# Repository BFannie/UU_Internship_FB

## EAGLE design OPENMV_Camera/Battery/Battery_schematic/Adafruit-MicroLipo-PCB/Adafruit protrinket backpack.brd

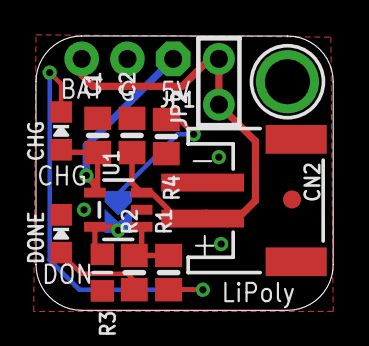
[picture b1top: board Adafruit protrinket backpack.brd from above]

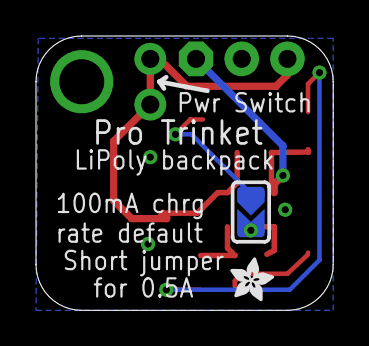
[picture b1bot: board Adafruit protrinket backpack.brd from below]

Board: 2 copper layers, 16.5 x 15.2 mm, 16 parts (2 on the bottom side), 8 nets.

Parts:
C1, C2: 10µF; 0805-NO
CHG: RED; CHIPLED_0805_NOOUTLINE
CN2: JSTPH; JSTPH2
DONE: GREEN; CHIPLED_0805_NOOUTLINE
FID1: FIDUCIAL""; FIDUCIAL_1MM
JP1: 1X03_ROUND_76
JP2: 1X02_ROUND
R1, R2: 1K; 0805-NO
R3: 10K\; _0805MP
R4: 2.5K; 0805-NO
SJ1: SOLDERJUMPER_ARROW_NOPASTE
U1: MCP73831T-2ACI/OT; SOT23-5
U$9: ADAFRUIT_2.5MM
U$10: MOUNTINGHOLE2.5; MOUNTINGHOLE_2.5_PLATED

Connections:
GND: C1.2, C2.2, CN2.1, DONE.C, JP1.2, R3.2, R4.2, U1.2
unnamed: CHG.C, R1.1
unnamed: R1.2, R2.2, U1.1
unnamed: R4.1, SJ1.1
unnamed: R3.1, SJ1.2, U1.5
unnamed: DONE.A, R2.1
VBAT: C2.1, CN2.2, JP1.3, JP2.1, JP2.2, U1.3
VBUS: C1.1, CHG.A, JP1.1, U1.4

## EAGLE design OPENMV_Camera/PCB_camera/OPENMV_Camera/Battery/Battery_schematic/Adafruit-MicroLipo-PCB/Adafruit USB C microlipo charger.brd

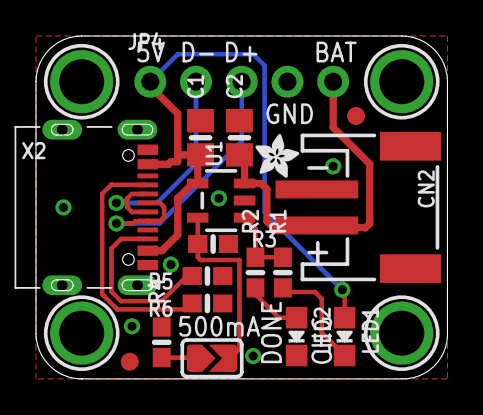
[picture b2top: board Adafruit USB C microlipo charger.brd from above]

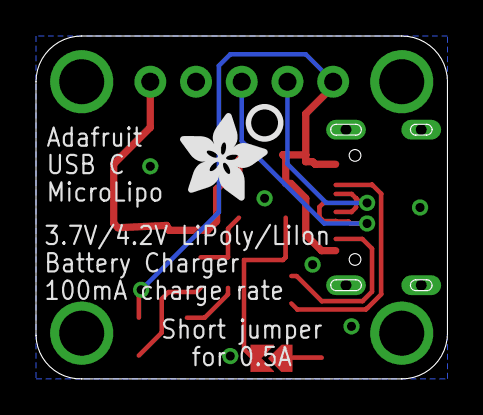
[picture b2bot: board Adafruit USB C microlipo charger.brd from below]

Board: 2 copper layers, 22.9 x 19.1 mm, 24 parts (2 on the bottom side), 12 nets.

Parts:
C1, C2: 10µF; 0805-NO@1
CN2: JSTPH; JSTPH2
FID1, FID2: FIDUCIAL""; FIDUCIAL_1MM
JP4: 1X05_ROUND_70
LED1: RED; CHIPLED_0805_NOOUTLINE
LED2: GREEN; CHIPLED_0805_NOOUTLINE
R1, R2: 470; 0603-NO
R3: 10K\; 0603-NO
R4: 2.2K; 0603-NO
R5, R6: 5.1K; 0603-NO
SJ1: SOLDERJUMPER_ARROW_NOPASTE
U1: MCP73831T-2ACI/OT; SOT23-5
U$2: ADAFRUIT_2.5MM
U$9, U$10, U$11, U$12: MOUNTINGHOLE2.5; MOUNTINGHOLE_2.5_PLATED
U$13: ADAFRUIT_5MM
U$16: PCBFEAT-REV-040
X2: USB_C_CUSB31-CFM2AX-01-X

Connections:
5V: C1.1, JP4.1, LED1.A, U1.4, X2.A4B9, X2.B4A9
CC1: R6.2, X2.A5
CC2: R5.2, X2.B5
D+: JP4.3, X2.A6, X2.B6
D-: JP4.2, X2.A7, X2.B7
GND: C1.2, C2.2, CN2.1, JP4.4, LED2.C, R3.2, R4.2, R5.1, R6.1, U1.2, X2.A1B12, X2.B1A12
unnamed: LED1.C, R1.1
unnamed: R1.2, R2.2, U1.1
unnamed: R4.1, SJ1.1
unnamed: R3.1, SJ1.2, U1.5
unnamed: LED2.A, R2.1
VBAT: C2.1, CN2.2, JP4.5, U1.3

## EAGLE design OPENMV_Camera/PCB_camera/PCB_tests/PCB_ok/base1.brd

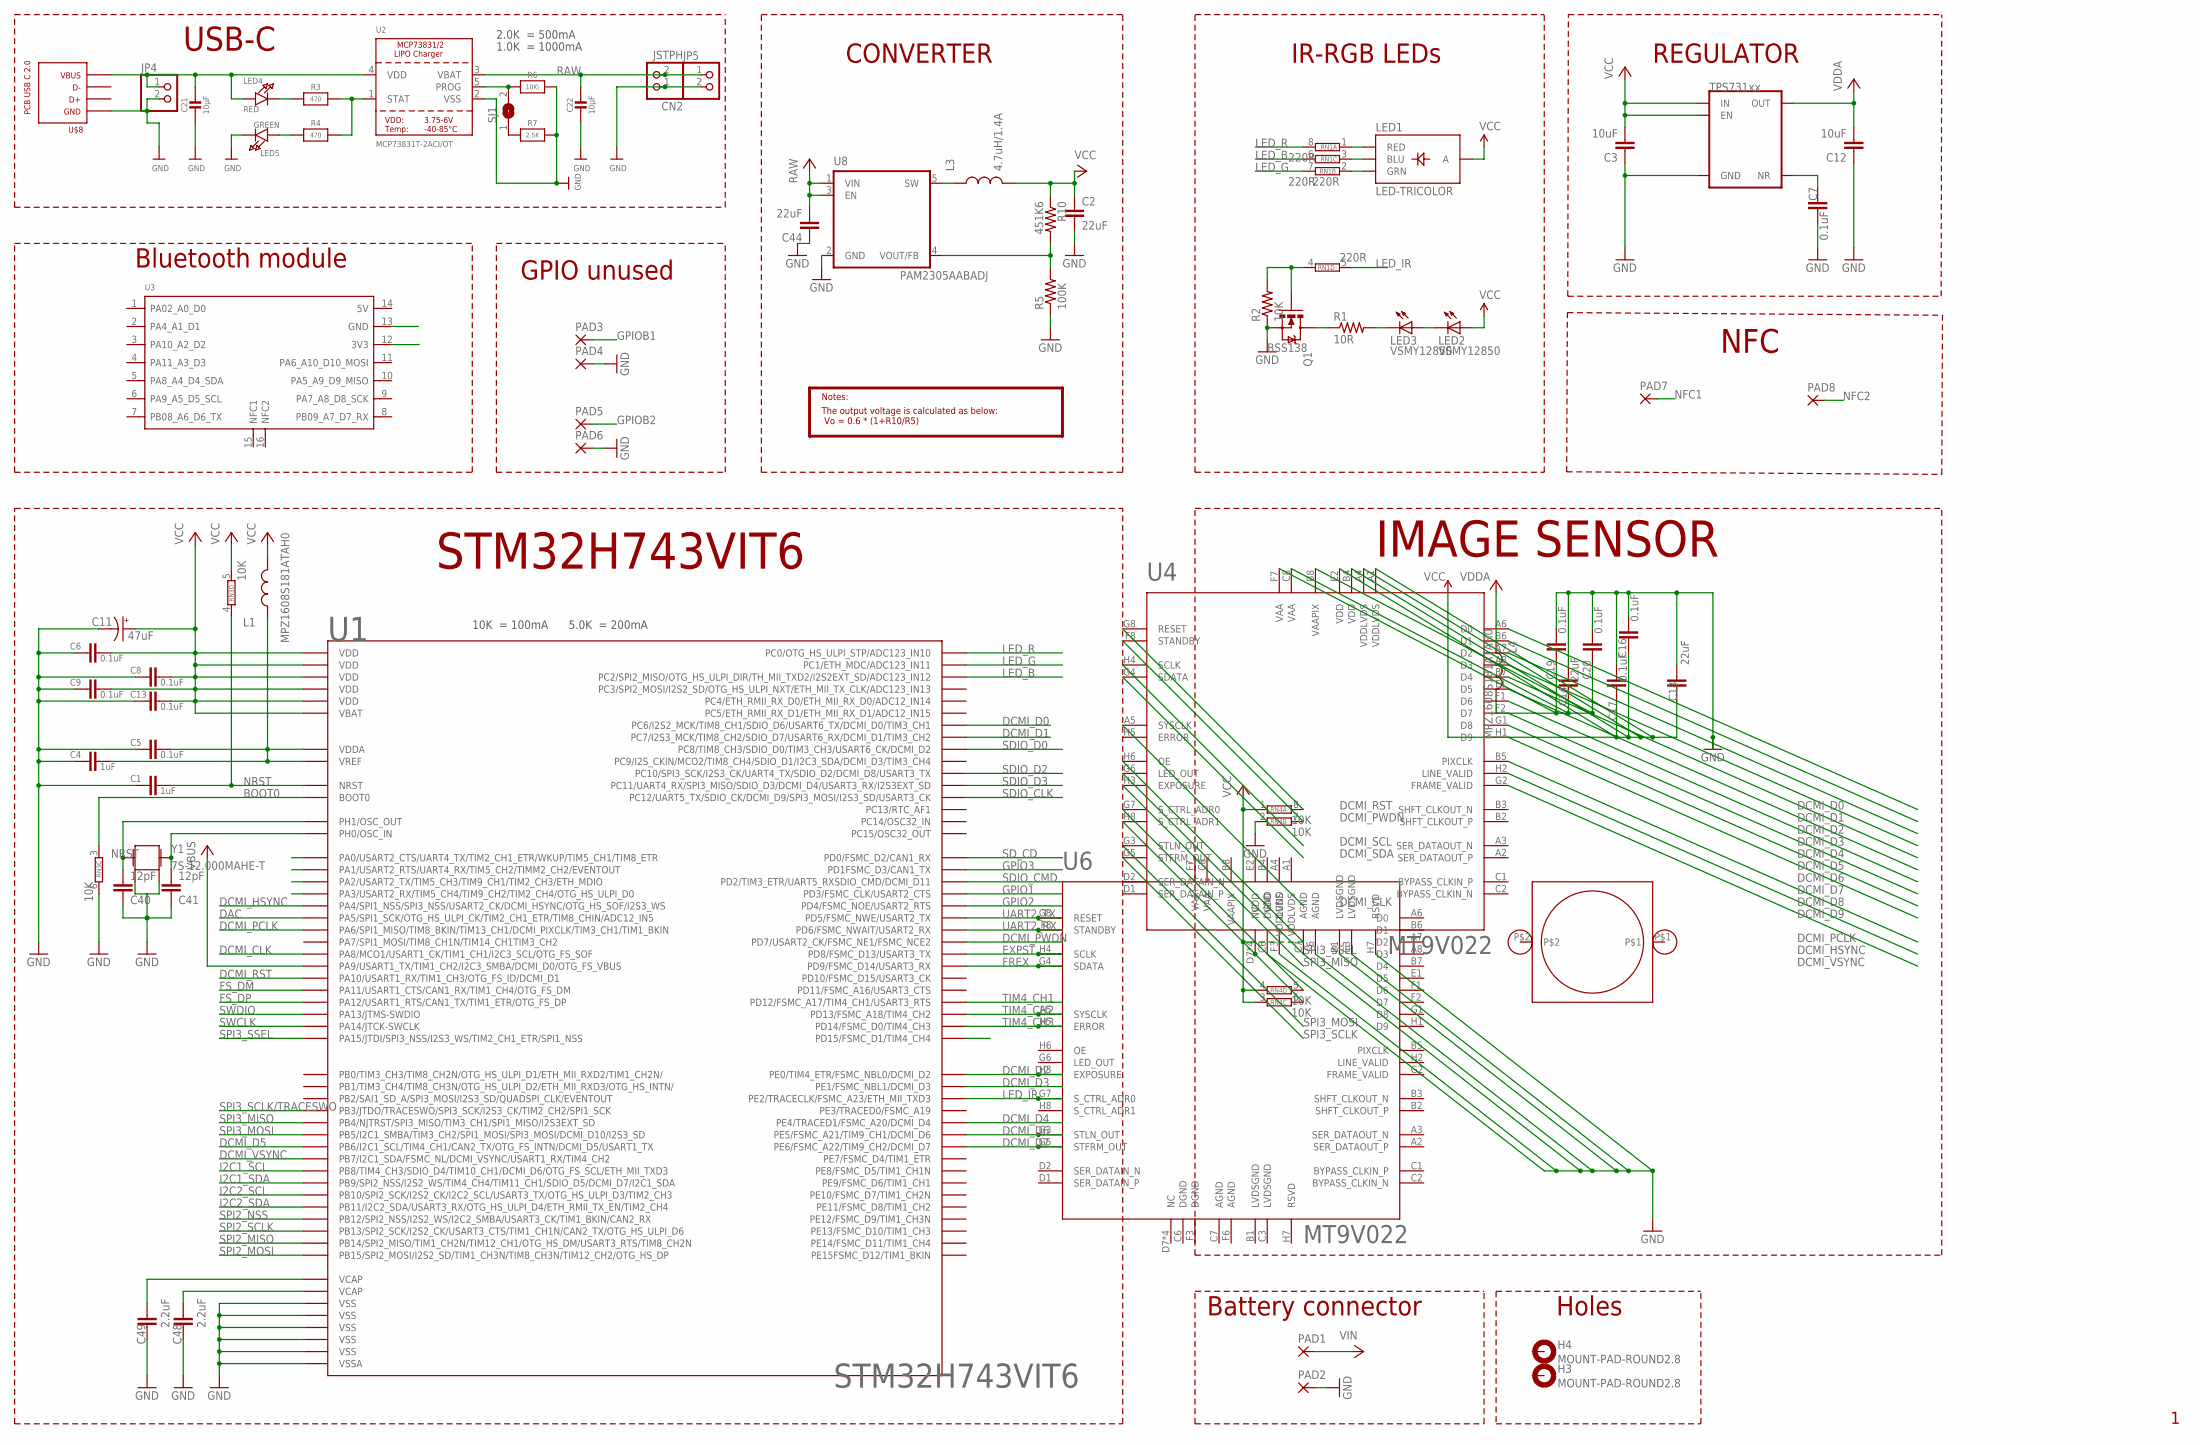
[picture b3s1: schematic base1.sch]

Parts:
C1, C4: 1uF; 0603-CAP
C2, C14, C18, C44: 22uF; 0805
C3, C12: 10uF; 0805
C5, C6, C7, C8, C9, C13: 0.1uF; 0603-CAP
C11: 47uF; EIA3216
C16, C17, C19, C20: 0.1uF; 0402-CAP
C21, C22: 10µF; 0805-NO
C40, C41: 12pF; 0603-CAP
C48, C49: 2.2uF; 0603-CAP
CN2: JSTPH; JSTPH2
H3, H4: MOUNT-PAD-ROUND2.8; 2,8-PAD
JP4, JP5: HEADER-1X2ROUND; 1X02_ROUND
L1, L4: MPZ1608S181ATAH0; 0603
L3: 4.7uH/1.4A; 1007
LED1: LED-TRICOLOR; LED-TRICOLOR-SMD-MF
LED2, LED3: VSMY12850; LED-1206
LED4: RED; CHIPLED_0805_NOOUTLINE
LED5: GREEN; CHIPLED_0805_NOOUTLINE
LM1: LENSMOUNT20MM; LENSMOUNT-20MM
PAD1, PAD2, PAD3, PAD4, PAD5, PAD6, PAD7, PAD8: SMD2; SMD1,27-2,54
Q1: BSS138; SOT23-3
R1: 10R; 0603-RES
R2: 10K; 0603-RES
R3, R4: 470; 0805-NO
R5: 100K; 0603-RES
R6: 10K\; 0805-NO
R7: 2.5K; 0805-NO
R10: 451K6; 0603-RES
RN1: 220R; EXBV8V
RN3, RN4: 10K; EXBV8V
SJ1: SOLDERJUMPER; SOLDERJUMPER_ARROW_NOPASTE
U1: STM32H743VIT6; LQFP100
U2: MCP73831T-2ACI/OT; SOT23-5
U3: MOUDLE-SEEEDUINO-XIAO-NRF52840-SENSE-SMD; MOUDLE16P-SMD-2.54-21X17.8MM
U4, U6: MT9V022; IBGA52
U5: TPS731XX; SOT23-5
U8: PAM2305AABADJ; TSOT25
U$8: PCB_USB_C_2.0DS_2; USB_TYPE_C_DS_2
Y1: 7S-12.000MAHE-T; CRYSTAL-2.5X2.0

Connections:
BOOT0: RN3.3 (1), U1.94 (BOOT0)
DAC: U1.29 (PA5/SPI1_SCK/OTG_HS_ULPI_CK/TIM2_CH1_ET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)
DCMI_CLK: U1.67 (PA8/MCO1/USART1_CK/TIM1_CH1/I2C3_SCL/OT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), U4.A5 (SYSCLK)
DCMI_D0: U1.63 (PC6/I2S2_MCK/TIM8_CH1/SDIO_D6/USART6_TX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), U4.A6 (D0)
DCMI_D1: U1.64 (PC7/I2S3_MCK/TIM8_CH2/SDIO_D7/USART6_RX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), U4.B6 (D1)
DCMI_D2: U1.97 (PE0/TIM4_ETR/FSMC_NBL0/DCMI_D2), U4.A7 (D2), U6.H3 (EXPOSURE)
DCMI_D3: U1.98 (PE1/FSMC_NBL1/DCMI_D3), U4.A8 (D3)
DCMI_D4: U1.3 (PE4/TRACED1/FSMC_A20/DCMI_D4), U4.B7 (D4)
DCMI_D5: U1.92 (PB6/I2C1_SCL/TIM4_CH1/CAN2_TX/OTG_FS_IN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), U4.E1 (D5)
DCMI_D6: U1.4 (PE5/FSMC_A21/TIM9_CH1/DCMI_D6), U4.F1 (D6), U6.G3 (STLN_OUT)
DCMI_D7: U1.5 (PE6/FSMC_A22/TIM9_CH2/DCMI_D7), U4.F2 (D7), U6.G5 (STFRM_OUT)
DCMI_D8: U4.G1 (D8)
DCMI_D9: U4.H1 (D9)
DCMI_HSYNC: U1.28 (PA4/SPI1_NSS/SPI3_NSS/USART2_CK/DCMI_HS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), U4.H2 (LINE_VALID)
DCMI_PCLK: U1.30 (PA6/SPI1_MISO/TIM8_BKIN/TIM13_CH1/DCMI_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), U4.B5 (PIXCLK)
DCMI_PWDN: RN4.7 (2), U1.88 (PD7/USART2_CK/FSMC_NE1/FSMC_NCE2), U4.F8 (STANDBY)
DCMI_RST: RN4.8 (2), U1.69 (PA10/USART1_RX/TIM1_CH3/OTG_FS_ID/DCMI_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), U4.G8 (RESET)
DCMI_SCL: U4.H4 (SCLK)
DCMI_SDA: U4.G4 (SDATA)
DCMI_VSYNC: U1.93 (PB7/I2C1_SDA/FSMC_NL/DCMI_VSYNC/USART1_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), U4.G2 (FRAME_VALID)
EXPST: U1.55 (PD8/FSMC_D13/USART3_TX), U6.H4 (SCLK)
FREX: U1.56 (PD9/FSMC_D14/USART3_RX), U6.G4 (SDATA)
FS_DM: U1.70 (PA11/USART1_CTS/CAN1_RX/TIM1_CH4/OTG_FS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)
FS_DP: U1.71 (PA12/USART1_RTS/CAN1_TX/TIM1_ETR/OTG_FS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)
GND: C1.2, C2.2, C3.1, C4.2, C5.2, C6.2, C7.2, C8.2, C9.2, C11.C (-), C12.1, C13.2, C14.1, C16.2, C17.2, C18.1, C19.2, C20.2, C21.2, C22.2, C40.1, C41.1, C44.1, C48.2, C49.2, CN2.1, JP4.2, JP5.2, LED5.C, PAD2.1, PAD4.1, PAD6.1, Q1.2 (S), R2.1, R5.1, R6.2, R7.2, RN3.6 (2), RN4.2 (1), U1.10 (VSS), U1.19 (VSSA), U1.26 (VSS), U1.49 (VSS), U1.74 (VSS), U1.99 (VSS), U2.2 (VSS), U4.B1 (LVDSGND), U4.C3 (LVDSGND), U4.C6 (DGND), U4.C7 (AGND), U4.F3 (DGND), U4.F6 (AGND), U4.H7 (RSVD), U5.2 (GND), U8.2 (GND), U$8.A4 (VBUS), U$8.A9 (VBUS), U$8.B4 (VBUS), U$8.B9 (VBUS), Y1.2, Y1.4
GPIO1: U1.84 (PD3/FSMC_CLK/USART2_CTS)
GPIO2: U1.85 (PD4/FSMC_NOE/USART2_RTS)
GPIO3: U1.82 (PD1FSMC_D3/CAN1_TX)
GPIOB1: PAD3.1
GPIOB2: PAD5.1
I2C1_SCL: U1.95 (PB8/TIM4_CH3/SDIO_D4/TIM10_CH1/DCMI_D6/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)
I2C1_SDA: U1.96 (PB9/SPI2_NSS/I2S2_WS/TIM4_CH4/TIM11_CH1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)
I2C2_SCL: U1.46 (PB10/SPI2_SCK/I2S2_CK/I2C2_SCL/USART3_T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)
I2C2_SDA: U1.47 (PB11/I2C2_SDA/USART3_RX/OTG_HS_ULPI_D4/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)
LED_B: RN1.6 (2), U1.17 (PC2/SPI2_MISO/OTG_HS_ULPI_DIR/TH_MII_TX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)
LED_G: RN1.7 (2), U1.16 (PC1/ETH_MDC/ADC123_IN11)
LED_IR: RN1.5 (2), U1.1 (PE2/TRACECLK/FSMC_A23/ETH_MII_TXD3), U6.G7 (S_CTRL_ADR0)
LED_R: RN1.8 (2), U1.15 (PC0/OTG_HS_ULPI_STP/ADC123_IN10)
unnamed: LED4.C, R3.1
unnamed: C40.2, U1.13 (PH1/OSC_OUT), Y1.3 (2)
unnamed: R3.2, R4.2, U2.1 (STAT)
unnamed: C41.2, U1.12 (PH0/OSC_IN), Y1.1
unnamed: Q1.1 (G), R2.2, RN1.4 (1)
unnamed: LED1.B (BLU), RN1.3 (1)
unnamed: LED1.R (RED), RN1.1
unnamed: LED1.G (GRN), RN1.2 (1)
unnamed: LED3.C, R1.2
unnamed: C7.1, U5.4 (NR)
unnamed: C4.1, C5.1, L1.1, U1.20 (VREF), U1.21 (VDDA)
unnamed: R5.2, R10.2, U8.4 (VOUT/FB)
unnamed: Q1.3 (D), R1.1
unnamed: R6.1, SJ1.2, U2.5 (PROG)
unnamed: LED5.A, R4.1
unnamed: LED2.C, LED3.A
unnamed: R7.1, SJ1.1
unnamed: RN4.5 (2), U4.G7 (S_CTRL_ADR0)
unnamed: RN4.6 (2), U4.D7 (NC), U4.H8 (S_CTRL_ADR1)
NRST: C1.1, RN3.4 (1), U1.14 (NRST)
RAW: C22.1, C44.2, CN2.2, JP5.1, U2.3 (VBAT), U8.1 (VIN), U8.3 (EN)
SDIO_CLK: U1.80 (PC12/UART5_TX/SDIO_CK/DCMI_D9/SPI3_MOSI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)
SDIO_CMD: U1.83 (PD2/TIM3_ETR/UART5_RXSDIO_CMD/DCMI_D11)
SDIO_D0: U1.65 (PC8/TIM8_CH3/SDIO_D0/TIM3_CH3/USART6_CK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)
SDIO_D2: U1.78 (PC10/SPI3_SCK/I2S3_CK/UART4_TX/SDIO_D2/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)
SDIO_D3: U1.79 (PC11/UART4_RX/SPI3_MISO/SDIO_D3/DCMI_D4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)
SD_CD: U1.81 (PD0/FSMC_D2/CAN1_RX)
SPI2_MISO: U1.53 (PB14/SPI2_MISO/TIM1_CH2N/TIM12_CH1/OTG_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)
SPI2_MOSI: U1.54 (PB15/SPI2_MOSI/I2S2_SD/TIM1_CH3N/TIM8_C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)
SPI2_NSS: U1.51 (PB12/SPI2_NSS/I2S2_WS/I2C2_SMBA/USART3_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)
SPI2_SCLK: U1.52 (PB13/SPI2_SCK/I2S2_CK/USART3_CTS/TIM1_C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)
SPI3_MISO: U1.90 (PB4/NJTRST/SPI3_MISO/TIM3_CH1/SPI1_MISO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), U4.H3 (EXPOSURE)
SPI3_MOSI: U1.91 (PB5/I2C1_SMBA/TIM3_CH2/SPI1_MOSI/SPI3_M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), U4.G3 (STLN_OUT)
SPI3_SCLK: U4.G5 (STFRM_OUT)
SPI3_SCLK/TRACESWO: U1.89 (PB3/JTDO/TRACESWO/SPI3_SCK/I2S3_CK/TIM2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)
SPI3_SSEL: U1.77 (PA15/JTDI/SPI3_NSS/I2S3_WS/TIM2_CH1_ETR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), U4.G6 (LED_OUT)
SW: L3.1, U8.5 (SW)
SWCLK: U1.76 (PA14/JTCK-SWCLK)
SWDIO: U1.72 (PA13/JTMS-SWDIO)
TIM4_CH1: U1.59 (PD12/FSMC_A17/TIM4_CH1/USART3_RTS)
TIM4_CH2: U1.60 (PD13/FSMC_A18/TIM4_CH2), U6.A5 (SYSCLK)
TIM4_CH3: U1.61 (PD14/FSMC_D0/TIM4_CH3), U6.H5 (ERROR)
UART2_RX: U1.87 (PD6/FSMC_NWAIT/USART2_RX), U6.F8 (STANDBY)
UART2_TX: U1.86 (PD5/FSMC_NWE/USART2_TX), U6.G8 (RESET)
VAA: C14.2, C19.1, C20.1, L4.2, U4.B8 (VAAPIX), U4.C8 (VAA), U4.F7 (VAA)
VBAT: C2.1, C3.2, C6.1, C8.1, C9.1, C11.A (+), C13.1, C16.1, C17.1, C18.2, L1.2, L3.2, LED1.A, LED2.A, R10.1, RN3.5 (2), RN4.1, RN4.3 (1), RN4.4 (1), U1.6 (VBAT), U1.11 (VDD), U1.27 (VDD), U1.50 (VDD), U1.75 (VDD), U1.100 (VDD), U4.A1 (VDDLVDS), U4.A4 (VDDLVDS), U4.B4 (VDD), U4.E2 (VDD), U4.H6 (OE), U5.1 (IN), U5.3 (EN)
VBUS: U1.68 (PA9/USART1_TX/TIM1_CH2/I2C3_SMBA/DCMI_D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)
VCAP1: C49.1, U1.48 (VCAP)
VCAP2: C48.1, U1.73 (VCAP)
VDD: C21.1, JP4.1, LED4.A, U2.4 (VDD), U$8.A1 (GND), U$8.A12 (GND), U$8.B1 (GND), U$8.B12 (GND)
VDDA: C12.2, L4.1, U5.5 (OUT)
VIN: PAD1.1

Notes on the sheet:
STM32H743VIT6
IR-RGB LEDs
USB-C
Battery connector
The output voltage is calculated as below: Vo = 0.6 * (1+R10/R5)
Notes:
10K = 100mA
5.0K = 200mA
2.0K = 500mA
1.0K = 1000mA
CONVERTER
REGULATOR
GPIO unused
Bluetooth module
IMAGE SENSOR
Holes
NFC

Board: 2 copper layers, 67 parts (0 on the bottom side), 51 nets, no tracks yet.

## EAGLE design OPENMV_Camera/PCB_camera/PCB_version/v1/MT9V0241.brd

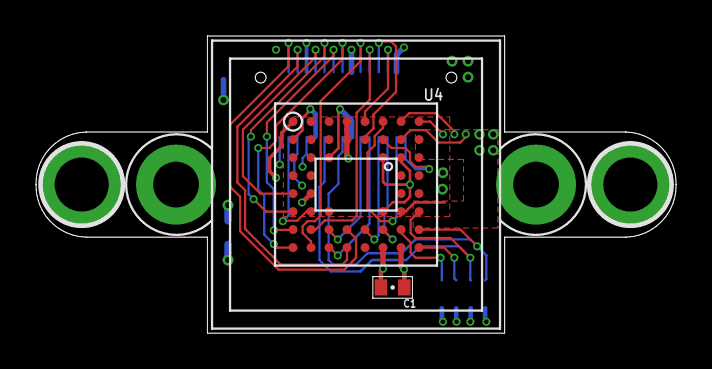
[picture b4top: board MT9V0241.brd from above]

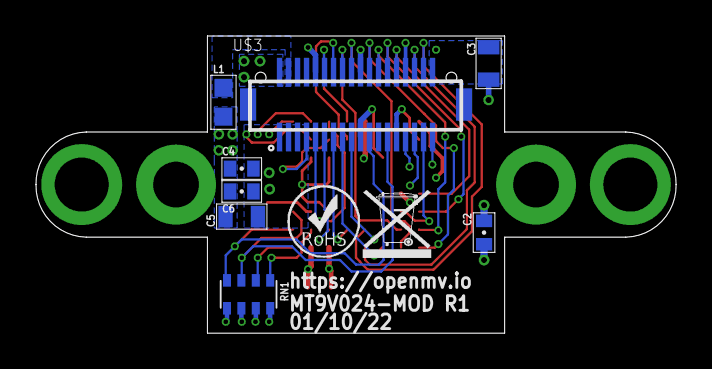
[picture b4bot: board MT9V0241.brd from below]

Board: 4 copper layers, 35.6 x 16.5 mm, 13 parts (10 on the bottom side), 28 nets.

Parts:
C1, C2, C4, C6: 0.1uF; 0402-CAP
C3, C5: 22uF; 0805
L1: MPZ1608S181ATAH0; 0603
LM1: LENSMOUNT20MM; LENSMOUNT-20MM
RN1: 10K; EXBV8V
U4: MT9V022; IBGA52
U$1: WEEE
U$2: ROHS
U$3: DF12-36-DP

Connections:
DCMI_CLK: U4.A5, U$3.12
DCMI_D0: U4.A6, U$3.9
DCMI_D1: U4.B6, U$3.7
DCMI_D2: U4.A7, U$3.31
DCMI_D3: U4.A8, U$3.29
DCMI_D4: U4.B7, U$3.35
DCMI_D5: U4.E1, U$3.28
DCMI_D6: U4.F1, U$3.26
DCMI_D7: U4.F2, U$3.33
DCMI_D8: U4.G1, U$3.24
DCMI_D9: U4.H1, U$3.22
DCMI_HSYNC: U4.H2, U$3.18
DCMI_PCLK: U4.B5, U$3.14
DCMI_PWDN: RN1.7, U4.F8, U$3.25
DCMI_RST: RN1.8, U4.G8, U$3.21
DCMI_SCL: U4.H4, U$3.32
DCMI_SDA: U4.G4, U$3.34
DCMI_VSYNC: U4.G2, U$3.16
GND: C1.2, C2.2, C3.1, C4.2, C5.1, C6.2, RN1.2, U4.B1, U4.C3, U4.C6, U4.C7, U4.F3, U4.F6, U4.H7, U$3.5, U$3.19, U$3.27
unnamed: RN1.5, U4.G7
unnamed: RN1.6, U4.H8
SPI3_MISO: U4.H3, U$3.15
SPI3_MOSI: U4.G3, U$3.17
SPI3_SCLK: U4.G5, U$3.13
SPI3_SSEL: U4.G6, U$3.11
VAA: C4.1, C5.2, C6.1, L1.2, U4.B8, U4.C8, U4.F7
VCC: C1.1, C2.1, C3.2, RN1.1, RN1.3, RN1.4, U4.A1, U4.A4, U4.B4, U4.E2, U4.H6, U$3.2, U$3.10, U$3.20, U$3.30, U$3.36
VDDA: L1.1, U$3.4

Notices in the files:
parts and their libraries:
microbuilder: This work is placed in the public domain, and may be freely used for commercial and non-commercial work with the following conditions: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
WE_WIRL_Rev13.0: Copyright: Würth Elektronik
sfe: Licensing: CC v3.0 Share-Alike You are welcome to use this library for commercial purposes.
